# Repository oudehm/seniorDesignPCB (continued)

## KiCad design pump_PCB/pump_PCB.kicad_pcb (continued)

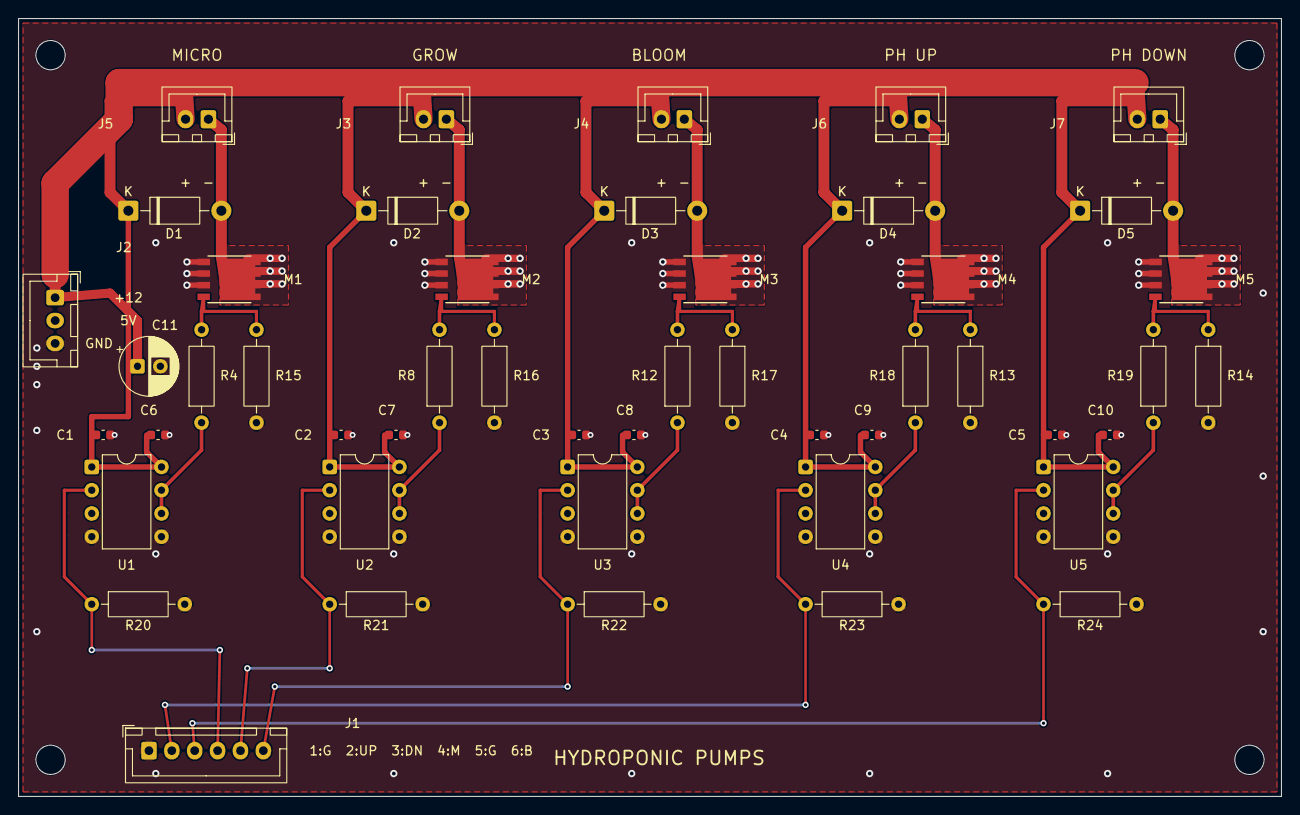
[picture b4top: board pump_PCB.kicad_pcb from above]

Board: 2 copper layers, 138.0 x 85.0 mm, 52 parts (0 on the bottom side), 22 nets.

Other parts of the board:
H1, H2, H3, H4: MountingHole_3.2mm_M3

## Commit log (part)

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2026-06-03 initial project structure
2026-06-03 brain PCB schematic in progress: power pins, decoupling caps, VCAP, crystals, reset, boot, SWD, UART, analog sensors, temp probes
2026-06-08 full schematic complete; minor warnings regarding labels
2026-06-08 brain PCB schematic: footprints assigned, ready for PCB layout
2026-06-08 initial PCB placementt
